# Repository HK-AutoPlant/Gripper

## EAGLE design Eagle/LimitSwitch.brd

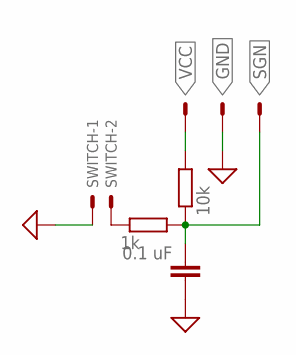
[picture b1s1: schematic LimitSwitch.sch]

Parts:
C1: 0.1 uF; C1206
INPUT: 22-23-2031
R3: 10k; R1206
R4: 1k; R1206
SWITCH: 22-23-2021

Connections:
GND: C1.2, INPUT.2, SWITCH.1
unnamed: R4.1, SWITCH.2
SGN: C1.1, INPUT.3, R3.1, R4.2
VCC: INPUT.1, R3.2

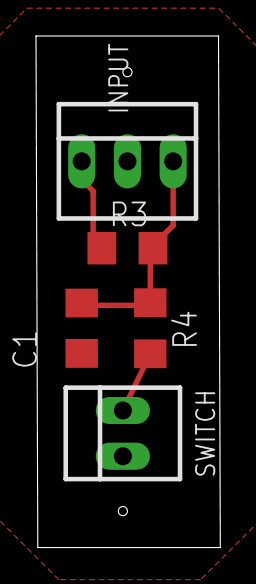
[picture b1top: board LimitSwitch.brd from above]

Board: 2 copper layers, 10.2 x 28.4 mm, 5 parts (0 on the bottom side), 4 nets.

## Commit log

2020-11-16 Add files via upload
    Circuit board of both limit switches
2020-11-16 Code for gripper actuation
    Test code with one main script (no classes since they are within the script).
